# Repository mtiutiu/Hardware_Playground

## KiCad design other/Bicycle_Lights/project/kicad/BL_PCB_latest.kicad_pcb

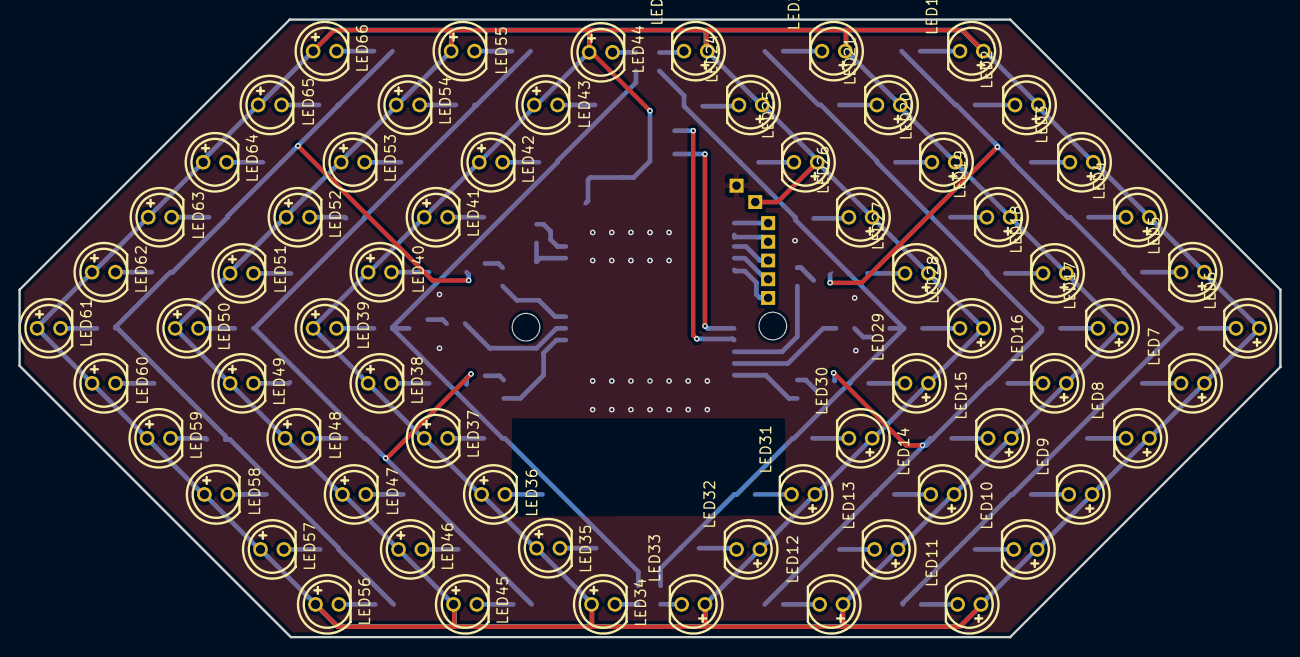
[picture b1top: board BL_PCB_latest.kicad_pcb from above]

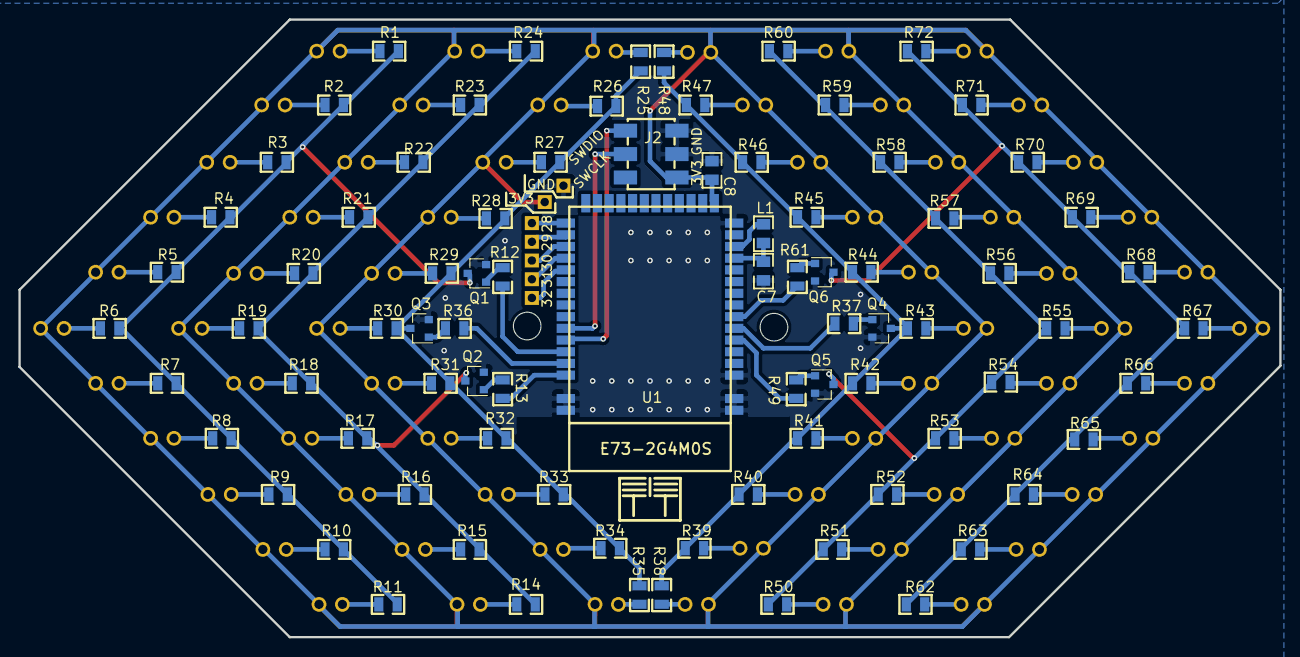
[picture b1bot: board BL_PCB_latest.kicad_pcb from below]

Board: 2 copper layers, 136.9 x 67.1 mm, 150 parts (6 on the bottom side), 90 nets.

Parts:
C7: 1u; 0805
C8: 10u; 0805
J2: SWD; H2X3-SMD-2.54
L1: 10uH; 0805
LED1, LED2, LED3, LED4, LED5, LED6, LED7, LED8, LED9, LED10, LED11, LED12, LED13, LED14, LED15, LED16, LED17, LED18, LED19, LED20, LED21, LED22, LED23, LED24, LED25, LED26, LED27, LED28, LED29, LED30, LED31, LED32, LED33, LED34, LED35, LED36, LED37, LED38, LED39, LED40, LED41, LED42, LED43, LED44, LED45, LED46, LED47, LED48, LED49, LED50, LED51, LED52, LED53, LED54, LED55, LED56, LED57, LED58, LED59, LED60, LED61, LED62, LED63, LED64, LED65, LED66: HL-503S45FC; LED-TH_BD5.0-P2.54-FD
LG: my_logo; ggeac4e8891367b2b2c
Q1, Q2, Q3, Q4, Q5, Q6: MMBT2222; SOT-23
R1, R2, R3, R4, R5, R6, R7, R8, R9, R10, R11, R14, R15, R16, R17, R18, R19, R20, R21, R22, R23, R24, R25, R26, R27, R28, R29, R30, R31, R32, R33, R34, R35, R38, R39, R40, R41, R42, R43, R44, R45, R46, R47, R48, R50, R51, R52, R53, R54, R55, R56, R57, R58, R59, R60, R62, R63, R64, R65, R66, R67, R68, R69, R70, R71, R72: 33; R0805
R12, R13, R36, R37, R49, R61: 1K; R0805
U1: E73-2G4M0S; E73-2G4M04S

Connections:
+3V3: C8.2, J2.1, LED1.1, LED2.1, LED3.1, LED4.1, LED5.1, LED6.1, LED7.1, LED8.1, LED9.1, LED10.1, LED11.1, LED12.1, LED13.1, LED14.1, LED15.1, LED16.1, LED17.1, LED18.1, LED19.1, LED20.1, LED21.1, LED22.1, LED23.1, LED24.1, LED25.1, LED26.1, LED27.1, LED28.1, LED29.1, LED30.1, LED31.1, LED32.1, LED33.1, LED34.1, LED35.1, LED36.1, LED37.1, LED38.1, LED39.1, LED40.1, LED41.1, LED42.1, LED43.1, LED44.1, LED45.1, LED46.1, LED47.1, LED48.1, LED49.1, LED50.1, LED51.1, LED52.1, LED53.1, LED54.1, LED55.1, LED56.1, LED57.1, LED58.1, LED59.1, LED60.1, LED61.1, LED62.1, LED63.1, LED64.1, LED65.1, LED66.1, U1.16
AL1: R12.1, U1.39
AL2: R13.1, U1.41
AL3: R36.1, U1.40
AR1: R37.1, U1.6
AR2: R49.1, U1.5
AR3: R61.1, U1.7
C7_2: C7.2, L1.1, U1.12
GND: C7.1, C8.1, J2.2, J2.3, Q1.2, Q2.2, Q3.2, Q4.2, Q5.2, Q6.2, U1.0, U1.1, U1.2, U1.15, U1.42, U1.43
L1_2: L1.2, U1.13
LED1_2: LED1.2, R1.2
LED2_2: LED2.2, R2.2
LED3_2: LED3.2, R3.2
LED4_2: LED4.2, R4.2
LED5_2: LED5.2, R5.2
LED6_2: LED6.2, R6.2
LED7_2: LED7.2, R7.2
LED8_2: LED8.2, R8.2
LED9_2: LED9.2, R9.2
LED10_2: LED10.2, R10.2
LED11_2: LED11.2, R11.2
LED23_2: LED23.2, R25.2
LED24_2: LED24.2, R26.2
LED25_2: LED25.2, R27.2
LED26_2: LED26.2, R28.2
LED27_2: LED27.2, R29.2
LED28_2: LED28.2, R30.2
LED29_2: LED29.2, R31.2
LED30_2: LED30.2, R32.2
LED31_2: LED31.2, R33.2
LED32_2: LED32.2, R34.2
LED33_2: LED33.2, R35.2
Q1_1: Q1.1, R12.2
Q2_3: Q2.3, R14.1, R15.1, R16.1, R17.1, R18.1, R19.1, R20.1, R21.1, R22.1, R23.1, R24.1
Q3_1: Q3.1, R36.2
Q4_3: Q4.3, R38.1, R39.1, R40.1, R41.1, R42.1, R43.1, R44.1, R45.1, R46.1, R47.1, R48.1
Q5_3: Q5.3, R50.1, R51.1, R52.1, R53.1, R54.1, R55.1, R56.1, R57.1, R58.1, R59.1, R60.1
Q6_3: Q6.3, R62.1, R63.1, R64.1, R65.1, R66.1, R67.1, R68.1, R69.1, R70.1, R71.1, R72.1
R1_1: Q1.3, R1.1, R2.1, R3.1, R4.1, R5.1, R6.1, R7.1, R8.1, R9.1, R10.1, R11.1
R13_2: Q2.1, R13.2
R14_2: LED12.2, R14.2
R15_2: LED13.2, R15.2
R16_2: LED14.2, R16.2
R17_2: LED15.2, R17.2
R18_2: LED16.2, R18.2
R19_2: LED17.2, R19.2
R20_2: LED18.2, R20.2
R21_2: LED19.2, R21.2
R22_2: LED20.2, R22.2
R23_2: LED21.2, R23.2
R24_2: LED22.2, R24.2
R25_1: Q3.3, R25.1, R26.1, R27.1, R28.1, R29.1, R30.1, R31.1, R32.1, R33.1, R34.1, R35.1
R37_2: Q4.1, R37.2
R38_2: LED34.2, R38.2
R39_2: LED35.2, R39.2
R40_2: LED36.2, R40.2
R41_2: LED37.2, R41.2
R42_2: LED38.2, R42.2
R43_2: LED39.2, R43.2
R44_2: LED40.2, R44.2
R45_2: LED41.2, R45.2
R46_2: LED42.2, R46.2
R47_2: LED43.2, R47.2
R48_2: LED44.2, R48.2
R49_2: Q5.1, R49.2
R50_2: LED45.2, R50.2
R51_2: LED46.2, R51.2
R52_2: LED47.2, R52.2
R53_2: LED48.2, R53.2
R54_2: LED49.2, R54.2
R55_2: LED50.2, R55.2
R56_2: LED51.2, R56.2
R57_2: LED52.2, R57.2
R58_2: LED53.2, R58.2
R59_2: LED54.2, R59.2
R60_2: LED55.2, R60.2
R61_2: Q6.1, R61.2
R62_2: LED56.2, R62.2
R63_2: LED57.2, R63.2
R64_2: LED58.2, R64.2
R65_2: LED59.2, R65.2
R66_2: LED60.2, R66.2
R67_2: LED61.2, R67.2
R68_2: LED62.2, R68.2
R69_2: LED63.2, R69.2
R70_2: LED64.2, R70.2
R71_2: LED65.2, R71.2
R72_2: LED66.2, R72.2
SWCLK: J2.5, U1.37
SWDIO: J2.4, U1.38

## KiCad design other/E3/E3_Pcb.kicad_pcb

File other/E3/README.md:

### Ender-3 Controller Board Remake

#### 3D renderings of pcb

Top view | Bottom view
------------ | -------------
 | 

Designed using **EasyEDA** and ported to **KiCAD** (**PCB** only) using the awesome [easyeda2kicad](<https://github.com/wokwi/easyeda2kicad>) tool.

#### Hardware revisions:

- 0.1 - initial design
- 0.2 - fixed/optimized power traces width
- 0.3 - changelog:
  - expose thermal pads
  - BOOT0 connect via pull-down resistor
  - simplified usb interface
  - added power support via USB for MCU

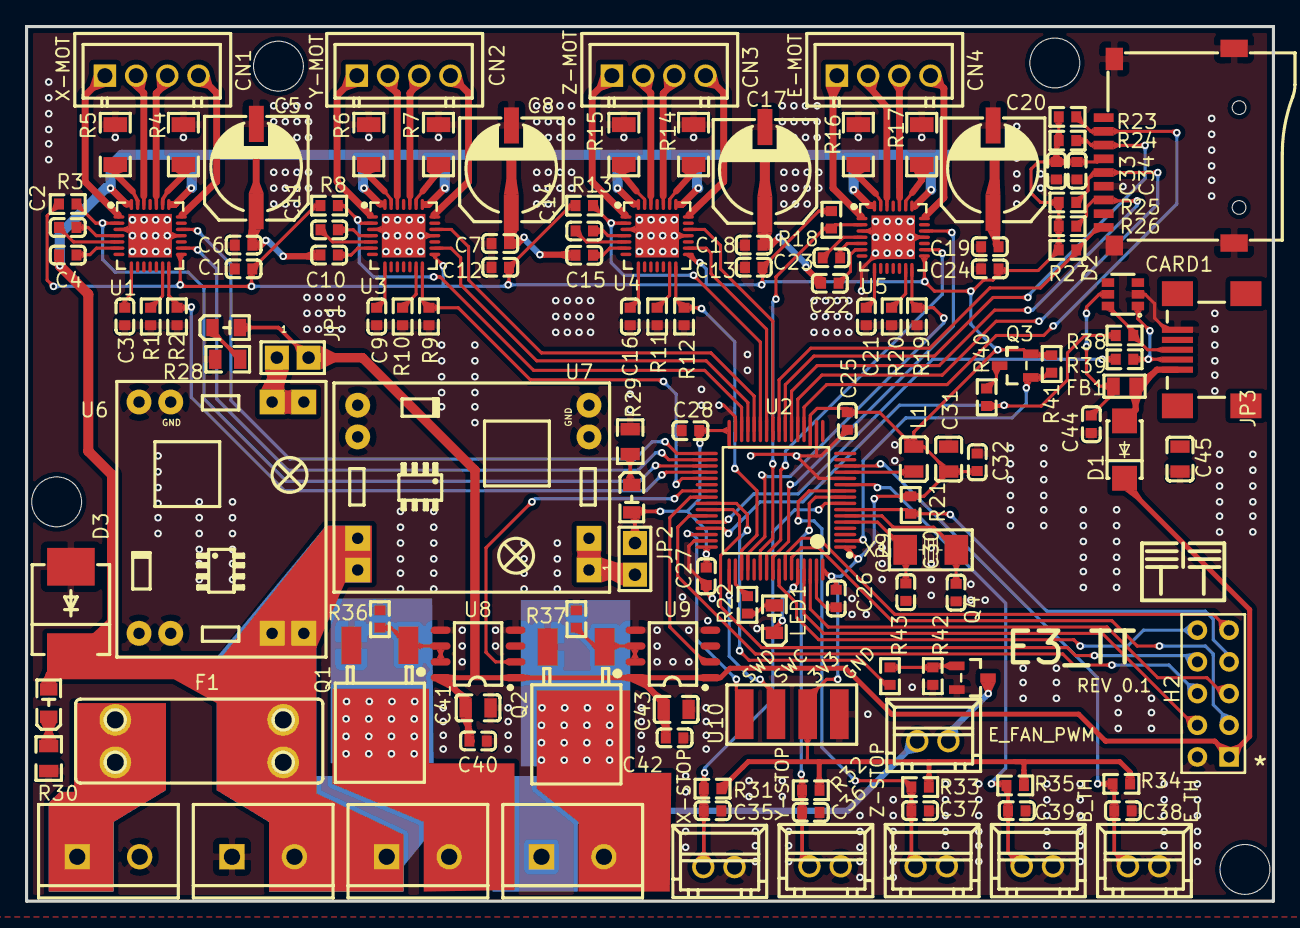
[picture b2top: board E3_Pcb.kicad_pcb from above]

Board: 2 copper layers, 99.9 x 70.1 mm, 133 parts (0 on the bottom side), 112 nets.

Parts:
ALG: my_logo; ggeac4e8891367b2b2c
C1, C4, C6, C7, C10, C12, C13, C15, C18, C19, C22, C24, C25, C26, C27, C28, C32, C34, C35, C36, C37, C40, C42, C44: 100nF; C0603
C2, C11, C14, C23: 22nF; C0603
C3, C9, C16, C21, C33: 4.7uF; C0603
C5, C8, C17, C20: 100uF; CAP-SMD_BD8.0-L8.3-W8.3-FD
C29, C30: 36pF; C0603
C31, C41, C43: 10uF; C0805
C38, C39: 10uF; C0603
C45: 4.7nF; C0805
CARD1: microSD; TF-SMD_TF-15×15
CN1, CN2, CN3, CN4: XH-4AK M; CONN-TH_4P-P2.50_XH-4A
CN5: X-STOP; CONN-TH_XH-2A
CN6: Y-STOP; CONN-TH_XH-2A
CN7: Z-STOP; CONN-TH_XH-2A
CN8: B_TH; CONN-TH_XH-2A
CN9: E_TH; CONN-TH_XH-2A
CN10: E_FAN_PWM; CONN-TH_XH-2A
D1: SS34; DO-214AC_L4.3-W2.7-LS5.3-RD
D2: NUP2114; TSOP-6_L3.0-W1.5-P0.95-LS2.8-BL
D3: SS36; SMC_L7.1-W6.2-LS8.1-RD
F1: 20A; KEYSTONE 3557-2
FB1: MH2029-300Y; L0805
H2: LCD; HDR-TH_10P-P2.54-V-R2-C5-S2.54
JP1, JP2: 1; JUMPER2
JP3: USB_MINI; USB-MINIB
L1: 22uH; L0805
LED1: STATUS; LED0805-RD
LED2: 5V_PWR; LED0805-RD
LED3: 3V3_PWR; LED0805-RD
LED4: PWR_IN; LED0805-RD
P1: PWR-IN; SCREWTERMINAL-5MM-2
P2: E_PWM; SCREWTERMINAL-5MM-2
P3: B_PWM; SCREWTERMINAL-5MM-2
P4: PWR-OUT; SCREWTERMINAL-5MM-2
Q1, Q2: IRLR8726TRPBF; TO-252-2_L6.6-W6.1-P4.57-LS9.9-BR-CW
Q3: IRLML2244TRPBF; SOT-23-3_L2.9-W1.6-P1.90-LS2.8-BR
Q4: IRLML6346TRPBF; SOT-23-3_L2.9-W1.6-P1.90-LS2.8-BR
R1, R2, R3, R8, R9, R10, R11, R12, R13, R18, R19, R20: 20K; R0603
R4, R5, R6, R7, R14, R15, R16, R17: 0.18; R1206
R21, R22, R34, R35: 4.7K; R0603
R23, R24, R25, R26, R31, R32, R33: 10K; R0603
R27: 1.8K; R0603
R28: 680; R0805
R29: 330; R0805
R30: 4.7K; R0805
R36, R37, R42: 100K; R0603
R38, R39: 27; R0603
R40, R41: 1.5K; R0603
R43: 10Ω; R0603
U1, U3, U4, U5: TMC2208-LA-T; QFN-28_L5.0-W5.0-P0.50-BL-EP
U2: STM32F103RCT6; LQFP-64_L10.0-W10.0-P0.50-LS12.0-BL
U6, U7: GND; MP1584 STEP DOWN MODULE - PCB
U8, U9: MCP1407-E/SN; SOP-8_L4.9-W3.9-P1.27-LS6.0-BL
U10: ICSP; SMD PIN HEADER 1X4
X1: 8MHz; OSC-SMD_L5.0-W3.2

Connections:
+3V3: C1.2, C12.2, C13.2, C24.2, C25.1, C26.1, C27.1, C28.1, C31.1, C32.2, C33.1, C34.1, CARD1.4, JP2.2, L1.1, LED3.2, Q3.2, R3.2, R8.2, R13.2, R18.2, R21.2, R23.2, R24.2, R25.2, R26.2, R27.2, R31.1, R32.1, R33.1, R34.2, R35.2, R41.2, U1.15, U2.1, U2.19, U2.32, U2.48, U2.64, U3.15, U4.15, U5.15, U10.2
+5V: C40.1, C41.1, C42.1, C43.1, D1.1, H2.1, JP1.2, LED2.2, U8.1, U8.8, U9.1, U9.8
+VB: C4.2, C5.1, C6.2, C7.2, C8.1, C10.2, C15.2, C17.1, C18.2, C19.2, C20.1, C22.2, CN10.1, D3.2, F1.2, LED4.2, P2.1, P3.1, P4.2, U1.22, U1.28, U3.22, U3.28, U4.22, U4.28, U5.22, U5.28, U6.2, U7.2
BED_PWM: U2.40, U9.2
C9_1: C9.1, U3.8
C10_1: C10.1, U3.6
C11_1: C11.1, U3.4
C11_2: C11.2, U3.5
C21_1: C21.1, U5.8
C22_1: C22.1, U5.6
C23_1: C23.1, U5.4
C23_2: C23.2, U5.5
C44_1: C44.1, D2.5, FB1.2
D2_1: D2.1, JP3.D-, R39.1
D2_6: D2.6, JP3.D+, R38.1
E0_DIR: U2.56, U5.19
E0_EN: R18.1, U2.54, U5.2
E0_OA1: CN4.3, U5.24
E0_OA2: CN4.4, U5.21
E0_OB1: CN4.2, U5.26
E0_OB2: CN4.1, U5.1
E0_STP: U2.55, U5.16
E0_UART: R19.2, U2.52, U5.14
F1_1: F1.1, P1.1
FAN_PWM: R43.1, U2.41
FB1_1: D1.2, FB1.1, JP3.VBUS
GND: C1.1, C3.2, C5.2, C6.1, C7.1, C8.2, C9.2, C12.1, C13.1, C16.2, C17.2, C18.1, C19.1, C20.2, C21.2, C24.1, C25.2, C26.2, C27.2, C28.2, C29.1, C30.1, C31.2, C32.1, C33.2, C34.2, C35.2, C36.2, C37.2, C38.2, C39.2, C40.2, C41.2, C42.2, C43.2, C44.2, C45.2, CARD1.6, CARD1.10, CARD1.11, CARD1.12, CARD1.13, CN5.2, CN6.2, CN7.2, CN8.2, CN9.2, D2.2, D3.1, H2.2, JP3.GND, LED1.1, P1.2, P4.1, Q1.3, Q2.3, Q4.2, R1.2, R2.1, R4.2, R5.2, R6.2, R7.2, R9.1, R10.2, R11.2, R12.1, R14.2, R15.2, R16.2, R17.2, R19.1, R20.2, R28.1, R29.1, R30.2, R36.1, R37.1, R42.1, U1.3, U1.18, U1.29, U2.12, U2.18, U2.31, U2.47, U2.60, U2.63, U3.3, U3.18, U3.29, U4.3, U4.18, U4.29, U5.3, U5.18, U5.29, U6.1, U6.4, U7.1, U7.4, U8.4, U8.5, U9.4, U9.5, U10.1
HE0_PWM: U2.39, U8.2
LCD_BEEP: H2.10, U2.57
LCD_CS: H2.4, U2.61
LCD_ENC_A: H2.6, U2.43
LCD_ENC_B: H2.8, U2.42
LCD_ENC_BTN: H2.9, U2.58
LCD_MOSI: H2.3, U2.59
LCD_SCK: H2.5, U2.62
Q1_2: P2.2, Q1.2
Q2_2: P3.2, Q2.2
Q3_3: Q3.3, R40.1
Q4_1: Q4.1, R42.2, R43.2
Q4_3: CN10.2, Q4.3
R10_1: R10.1, U3.13
R20_1: R20.1, U5.13
R22_2: LED1.2, R22.2
R28_2: LED2.1, R28.2
R29_2: LED3.1, R29.2
R30_1: LED4.1, R30.1
R37_2: Q2.1, R37.2, U9.6, U9.7
RESET: H2.7, R21.1, U2.7
SD_CS: CARD1.2, R23.1, U2.20
SD_DET: CARD1.9, R27.1, U2.24
SD_MISO: CARD1.7, R26.1, U2.22
SD_MOSI: CARD1.3, R24.1, U2.23
SD_SCK: CARD1.5, R25.1, U2.21
STATUS: R22.1, U2.50
SWCLK: U2.49, U10.3
SWDIO: U2.46, U10.4
TH0: C38.1, CN9.1, R34.1, U2.14
THB: C39.1, CN8.1, R35.1, U2.11
U1_4: C2.1, U1.4
U1_5: C2.2, U1.5
U1_6: C4.1, U1.6
U1_8: C3.1, U1.8
U1_13: R1.1, U1.13
U1_23: R4.1, U1.23
U1_27: R5.1, U1.27
U2_5: C29.2, U2.5, X1.1
U2_6: C30.2, U2.6, X1.2
U2_13: L1.2, U2.13
U3_23: R7.1, U3.23
U3_27: R6.1, U3.27
U4_4: C14.1, U4.4
U4_5: C14.2, U4.5
U4_6: C15.1, U4.6
U4_8: C16.1, U4.8
U4_13: R11.1, U4.13
U4_23: R14.1, U4.23
U4_27: R15.1, U4.27
U5_23: R17.1, U5.23
U5_27: R16.1, U5.27
U6_3: JP1.1, U6.3
U7_3: JP2.1, U7.3
U8_6: Q1.1, R36.2, U8.6, U8.7
USB_CONN: Q3.1, R41.1, U2.2
USB_D+: R38.2, R40.2, U2.45
USB_D-: R39.2, U2.44
X_DIR: U1.19, U2.33
X_EN: R3.1, U1.2, U2.35
X_OA1: CN1.3, U1.24
X_OA2: CN1.4, U1.21
X_OB1: CN1.2, U1.26
X_OB2: CN1.1, U1.1
X_STOP: C35.1, CN5.1, R31.2, U2.8
X_STP: U1.16, U2.34
X_UART: R2.2, U1.14, U2.36
Y_DIR: U2.28, U3.19
Y_EN: R8.1, U2.30, U3.2
Y_OA1: CN2.3, U3.24
Y_OA2: CN2.4, U3.21
Y_OB1: CN2.2, U3.26
Y_OB2: CN2.1, U3.1
Y_STOP: C36.1, CN6.1, R32.2, U2.9
Y_STP: U2.29, U3.16
Y_UART: R9.2, U2.37, U3.14
Z_DIR: U2.25, U4.19
Z_EN: R13.1, U2.27, U4.2
Z_OA1: CN3.3, U4.24
Z_OA2: CN3.4, U4.21
Z_OB1: CN3.2, U4.26
Z_OB2: CN3.1, U4.1
Z_STOP: C37.1, CN7.1, R33.2, U2.10
Z_STP: U2.26, U4.16
Z_UART: R12.2, U2.51, U4.14

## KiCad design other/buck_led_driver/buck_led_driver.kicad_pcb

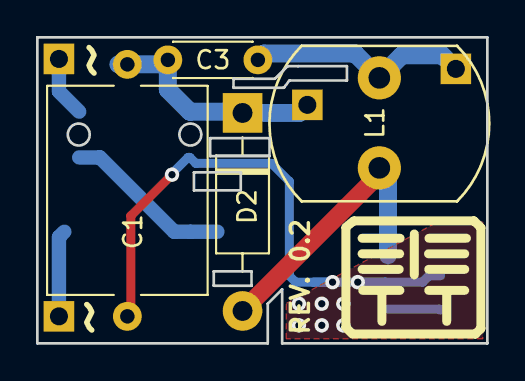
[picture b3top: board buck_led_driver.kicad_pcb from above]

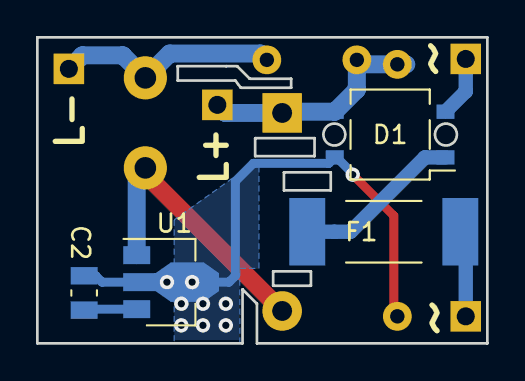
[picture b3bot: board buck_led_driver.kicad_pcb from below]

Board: 2 copper layers, 25.0 x 17.0 mm, 12 parts (4 on the bottom side), 8 nets.

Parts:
C1: 100n/400Vdc; C_Rect_L11.5mm_W8.8mm_P10.00mm_MKT
C2: 0.1u; C_0805_2012Metric
C3: 10n/100Vdc; C_Disc_D4.3mm_W1.9mm_P5.00mm
D1: MB10S; TO-269AA
D2: MUR160; D_DO-41_SOD81_P10.16mm_Horizontal
F1: 0.5A; R_2512_6332Metric
J1, J2: AC_IN; PinHeader_1x01_P2.54mm_Vertical
J3: LED+; PinHeader_1x01_P2.54mm_Vertical
J4: LED-; PinHeader_1x01_P2.54mm_Vertical
L1: 39mH; L_Radial_D12.0mm_P5.00mm_Neosid_SD12k_style2
U1: HV9922N8-G; SOT-89-3

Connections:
GND: C1.2, C2.1, D1.4, U1.2
unnamed: C1.1, C3.1, D1.3, D2.1, J3.1
unnamed: C2.2, U1.3
unnamed: C3.2, J4.1, L1.1
unnamed: D1.1, F1.1
unnamed: D1.2, J1.1
unnamed: D2.2, L1.2, U1.1
unnamed: F1.2, J2.1

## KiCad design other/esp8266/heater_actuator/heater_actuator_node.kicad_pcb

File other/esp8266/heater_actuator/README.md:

## ESP8266 heater actuator module

##### 3D renderings of pcb

Top view | Bottom view
------------ | -------------
 | 

**Description:**

This is a ESP8266 actuator node for controlling a heater or other appliances using a relay.

 **Kindly notice:**

The only thing I ask if using this project is to at least mention my name and if I don't ask too much you can also support my effort using the below button. Thanks for buying me a beer :).

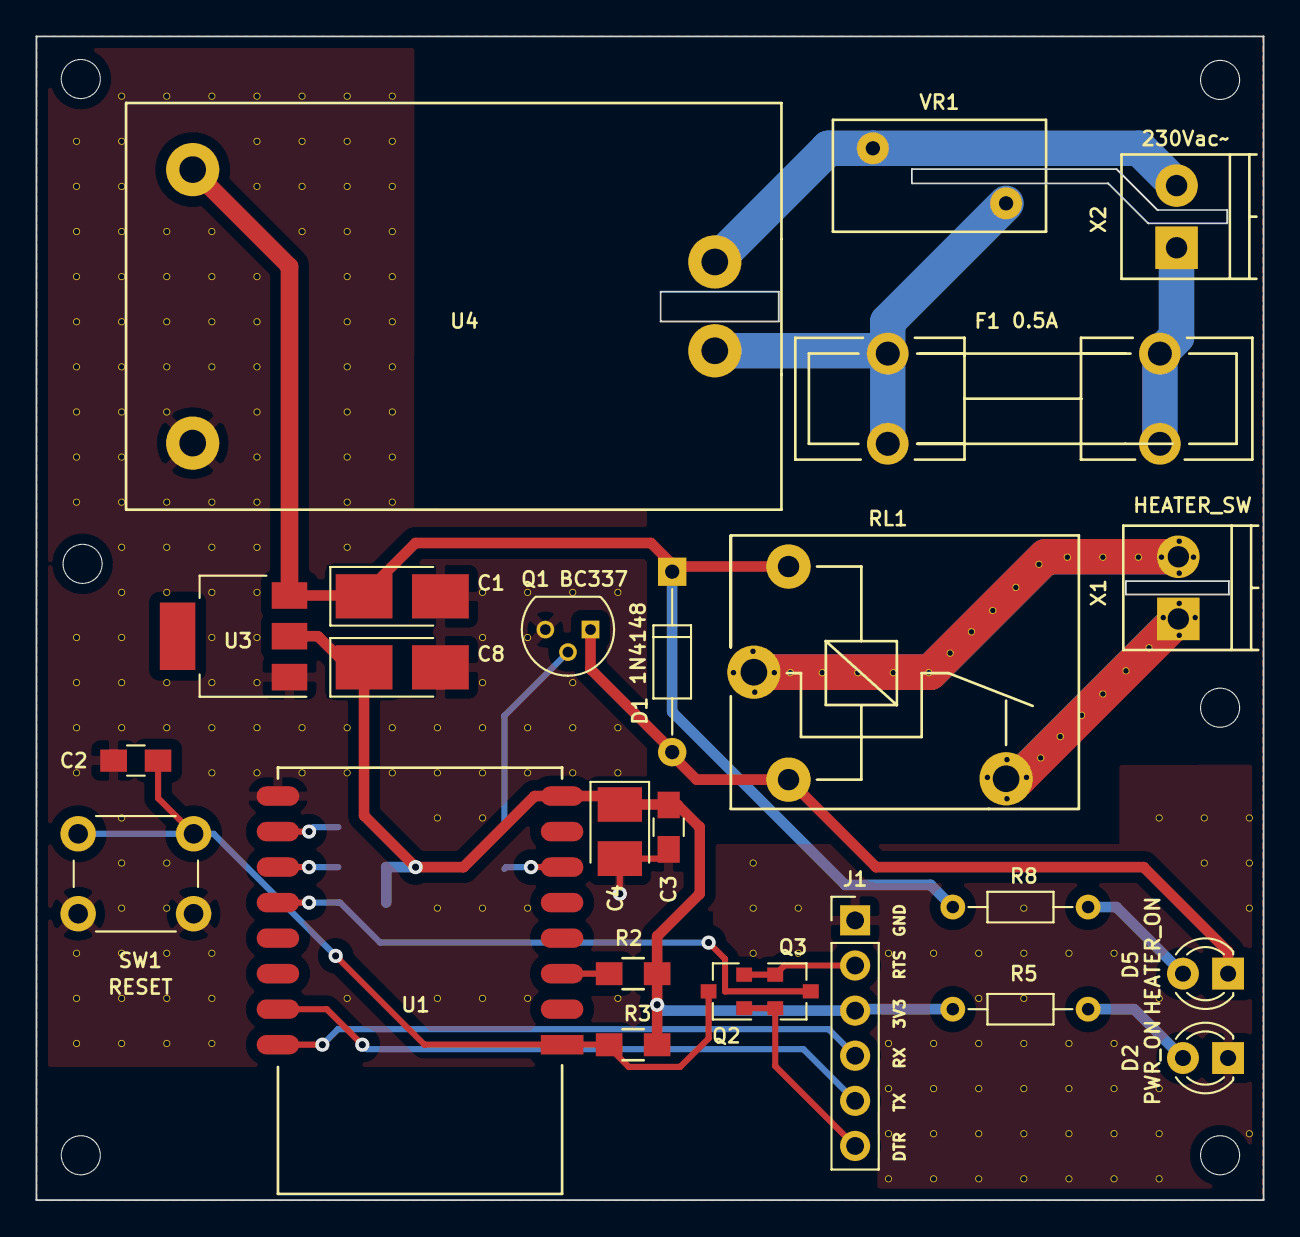
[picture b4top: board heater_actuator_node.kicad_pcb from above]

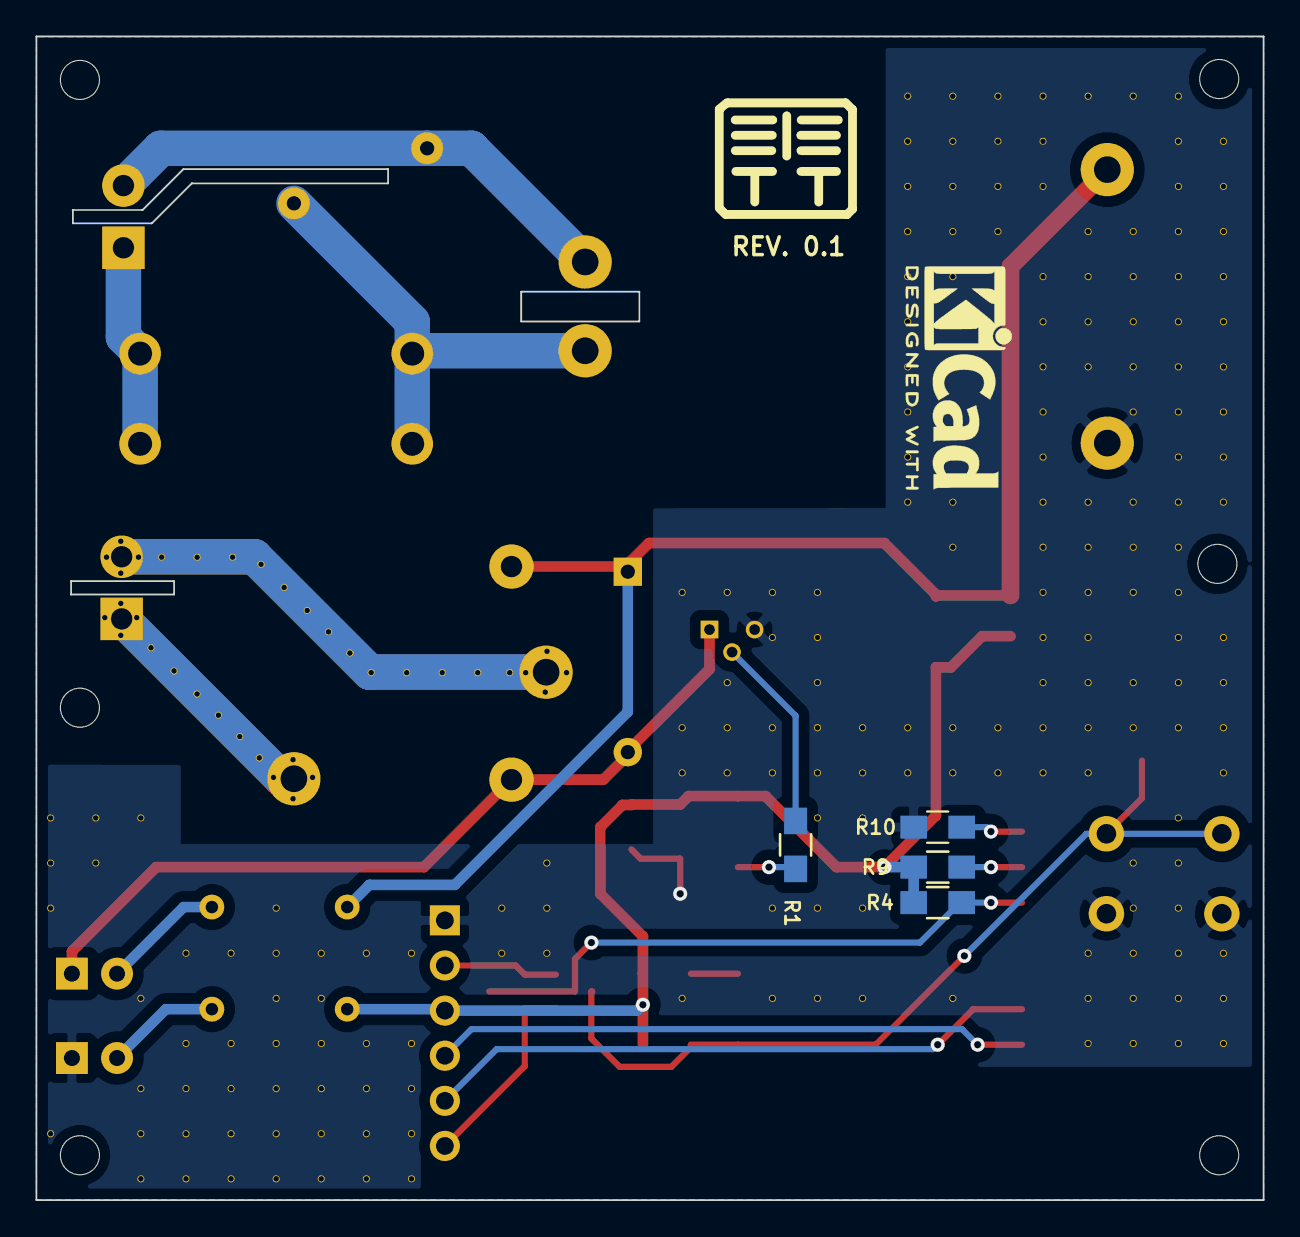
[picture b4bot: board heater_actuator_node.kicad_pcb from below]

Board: 2 copper layers, 69.1 x 65.5 mm, 255 parts (4 on the bottom side), 22 nets.

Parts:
C1, C8: 22u; CP_Tantalum_Case-B_EIA-3528-21_Hand
C2, C3: 100n; C_0805_HandSoldering
C4: 22u; CP_Tantalum_Case-B_EIA-3528-21_Reflow
D1: 1N4148; D_DO-35_SOD27_P10.16mm_Horizontal
D2: PWR_ON; LED_D3.0mm
D5: HEATER_ON; LED_D3.0mm
F1: 0.5A; Fuseholder5x20_horiz_open_lateral_Type-II
J1: Conn_01x06; Pin_Header_Straight_1x06_Pitch2.54mm
Q1: BC337; TO-92_Molded_Narrow
Q2, Q3: MMBT3904; SOT-23
R1: 5K6; R_0805_HandSoldering
R2, R3, R4, R9, R10: 10K; R_0805_HandSoldering
R5, R8: 330; R_Axial_DIN0204_L3.6mm_D1.6mm_P7.62mm_Horizontal
RL1: RM50-SP; RM50_SP
SW1: RESET; SW_PUSH_6mm
U1: ESP-12
U3: AMS1117-3.3; SOT-223
U4: HLK-PM01
V3_3, V3_4, V3_5, V3_6, V3_7, V3_8, V3_9, V3_10, V3_11, V3_14, V3_15, V3_16, V3_17, V3_21, V3_22, V3_23, V4_2, V4_3, V4_4, V4_5, V4_6, V4_7, V4_8, V4_9, V4_10, V4_11, V4_12, V4_13, V4_14, V4_15, V4_16, V4_18, V4_19, V4_20, V4_21, V4_22, V4_23, V5_2, V5_5, V5_6, V5_7, V5_8, V5_9, V5_11, V5_12, V5_13, V5_15, V5_16, V5_19, V5_20, V5_21, V5_22, V5_23, V6_2, V6_5, V6_6, V6_7, V6_8, V6_11, V6_12, V6_13, V6_14, V6_15, V6_16, V6_17, V6_21, V6_22, V6_23, V7_2, V7_3, V7_4, V7_6, V7_7, V7_8, V7_9, V7_10, V7_11, V7_12, V7_13, V7_14, V7_15, V7_16, V7_17, V8_2, V8_3, V8_4, V8_5, V8_16, V8_17, V9_2, V9_3, V9_4, V9_5, V9_6, V9_7, V9_8, V9_9, V9_10, V9_11, V9_12, V9_16, V9_17, V9_22, V10_2, V10_3, V10_4, V10_5, V10_6, V10_7, V10_8, V10_9, V10_10, V10_11, V10_16, V10_17, V11_16, V11_17, V11_18, V11_20, V11_22, V12_13, V12_14, V12_15, V12_16, V12_17, V12_18, V12_20, V12_22, V13_13, V13_14, V13_16, V13_17, V13_20, V13_22, V14_13, V14_15, V14_16, V14_17, V15_13, V15_16, V15_17, V15_22, V18_19, V18_20, V18_21, V19_20, V19_21, V21_21, V21_23, V21_24, V21_25, V21_26, V22_21, V22_23, V22_24, V22_25, V22_26, V23_21, V23_22, V23_23, V23_24, V23_25, V23_26, V24_20, V24_21, V24_22, V24_23, V24_24, V24_25, V24_26, V25_21, V25_23, V25_24, V25_25, V25_26, V26_21, V26_23, V26_24, V26_25, V26_26, V27_18, V27_18#2, V27_18#3, V27_18#4, V27_18#5, V27_18#6, V27_18#7, V27_18#8, V27_18#9, V27_18#10, V27_18#11, V27_18#12, V27_18#13, V27_18#14, V27_18#15, V27_18#16, V27_18#17, V27_18#18, V27_18#19, V27_18#20, V27_18#21, V27_18#22, V27_18#23, V27_18#24, V27_18#25, V27_18#26, V27_18#27, V27_18#28, V27_18#29, V27_18#30, V27_18#31, V27_18#32, V27_18#33, V27_18#34, V27_18#35, V27_18#36, V27_22, V27_24, V27_25, V27_26, V28_18, V28_19, V29_18, V29_19, V29_20, V29_25: AUTO_VIA; VIA_MATRIX
VR1: VAR10-300; RV_Disc_D12_W6.3_P7.5
X1: HEATER_SW; TerminalBlock_Pheonix_PT-3.5mm_2pol
X2: 230Vac~~; TerminalBlock_Pheonix_PT-3.5mm_2pol

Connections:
+3V3: C3.1, C4.1, C8.1, J1.3, R2.2, R3.2, R4.2, R5.1, R9.2, U1.8, U3.2
+5V: C1.1, D1.1, R8.1, RL1.A1, U3.3, U4.3
/DTR: J1.6, Q2.1, Q3.2
/EN: R2.1, U1.3
/GPIO0: Q3.3, R4.1, U1.12
/GPIO2: R9.1, U1.11
/GPIO15: R10.1, U1.10
/H_RELAY_CMD: R1.2, U1.6
/RESET: C2.1, Q2.3, R3.1, SW1.1, U1.1
/RTS: J1.2, Q2.2, Q3.1
/RX: J1.4, U1.16
/TX: J1.5, U1.15
GND: C1.2, C2.2, C3.2, C4.2, C8.2, D2.1, J1.1, Q1.3, R10.2, SW1.2, U1.9, U3.1, U4.4, V3_3.1, V3_4.1, V3_5.1, V3_6.1, V3_7.1, V3_8.1, V3_9.1, V3_10.1, V3_11.1, V3_14.1, V3_15.1, V3_16.1, V3_17.1, V3_21.1, V3_22.1, V3_23.1, V4_2.1, V4_3.1, V4_4.1, V4_5.1, V4_6.1, V4_7.1, V4_8.1, V4_9.1, V4_10.1, V4_11.1, V4_12.1, V4_13.1, V4_14.1, V4_15.1, V4_16.1, V4_18.1, V4_19.1, V4_20.1, V4_21.1, V4_22.1, V4_23.1, V5_2.1, V5_5.1, V5_6.1, V5_7.1, V5_8.1, V5_9.1, V5_11.1, V5_12.1, V5_13.1, V5_15.1, V5_16.1, V5_19.1, V5_20.1, V5_21.1, V5_22.1, V5_23.1, V6_2.1, V6_5.1, V6_6.1, V6_7.1, V6_8.1, V6_11.1, V6_12.1, V6_13.1, V6_14.1, V6_15.1, V6_16.1, V6_17.1, V6_21.1, V6_22.1, V6_23.1, V7_2.1, V7_3.1, V7_4.1, V7_6.1, V7_7.1, V7_8.1, V7_9.1, V7_10.1, V7_11.1, V7_12.1, V7_13.1, V7_14.1, V7_15.1, V7_16.1, V7_17.1, V8_2.1, V8_3.1, V8_4.1, V8_5.1, V8_16.1, V8_17.1, V9_2.1, V9_3.1, V9_4.1, V9_5.1, V9_6.1, V9_7.1, V9_8.1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
unnamed: D1.2, D5.1, Q1.1, RL1.A2
unnamed: D2.2, R5.2
unnamed: D5.2, R8.2
unnamed: F1.1, U4.1, VR1.1
unnamed: F1.2, X2.1
unnamed: Q1.2, R1.1
unnamed: RL1.11, V27_18.1, V27_18#2.1, V27_18#3.1, V27_18#18.1, V27_18#19.1, V27_18#20.1, V27_18#21.1, V27_18#22.1, V27_18#23.1, V27_18#24.1, V27_18#25.1, V27_18#26.1, V27_18#27.1, V27_18#28.1, V27_18#29.1, V27_18#30.1, V27_18#31.1, V27_18#32.1, V27_18#33.1, V27_18#34.1, V27_18#35.1, X1.2
unnamed: RL1.14, V27_18#4.1, V27_18#5.1, V27_18#6.1, V27_18#7.1, V27_18#8.1, V27_18#9.1, V27_18#10.1, V27_18#11.1, V27_18#12.1, V27_18#13.1, V27_18#14.1, V27_18#15.1, V27_18#16.1, V27_18#17.1, X1.1
unnamed: U4.2, VR1.2, X2.2

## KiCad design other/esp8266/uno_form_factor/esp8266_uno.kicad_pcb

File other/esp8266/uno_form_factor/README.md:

## ESP8266 Arduino UNO

##### 3D renderings of pcb

Top view | Bottom view
------------ | -------------
 | 

**Description:**

ESP8266 board in Arduino UNO format(support for ESP-12 series OR WROOM).

 **Kindly notice:**

The only thing I ask if using this project is to at least mention my name and if I don't ask too much you can also support my effort using the below button. Thanks for buying me a beer :).

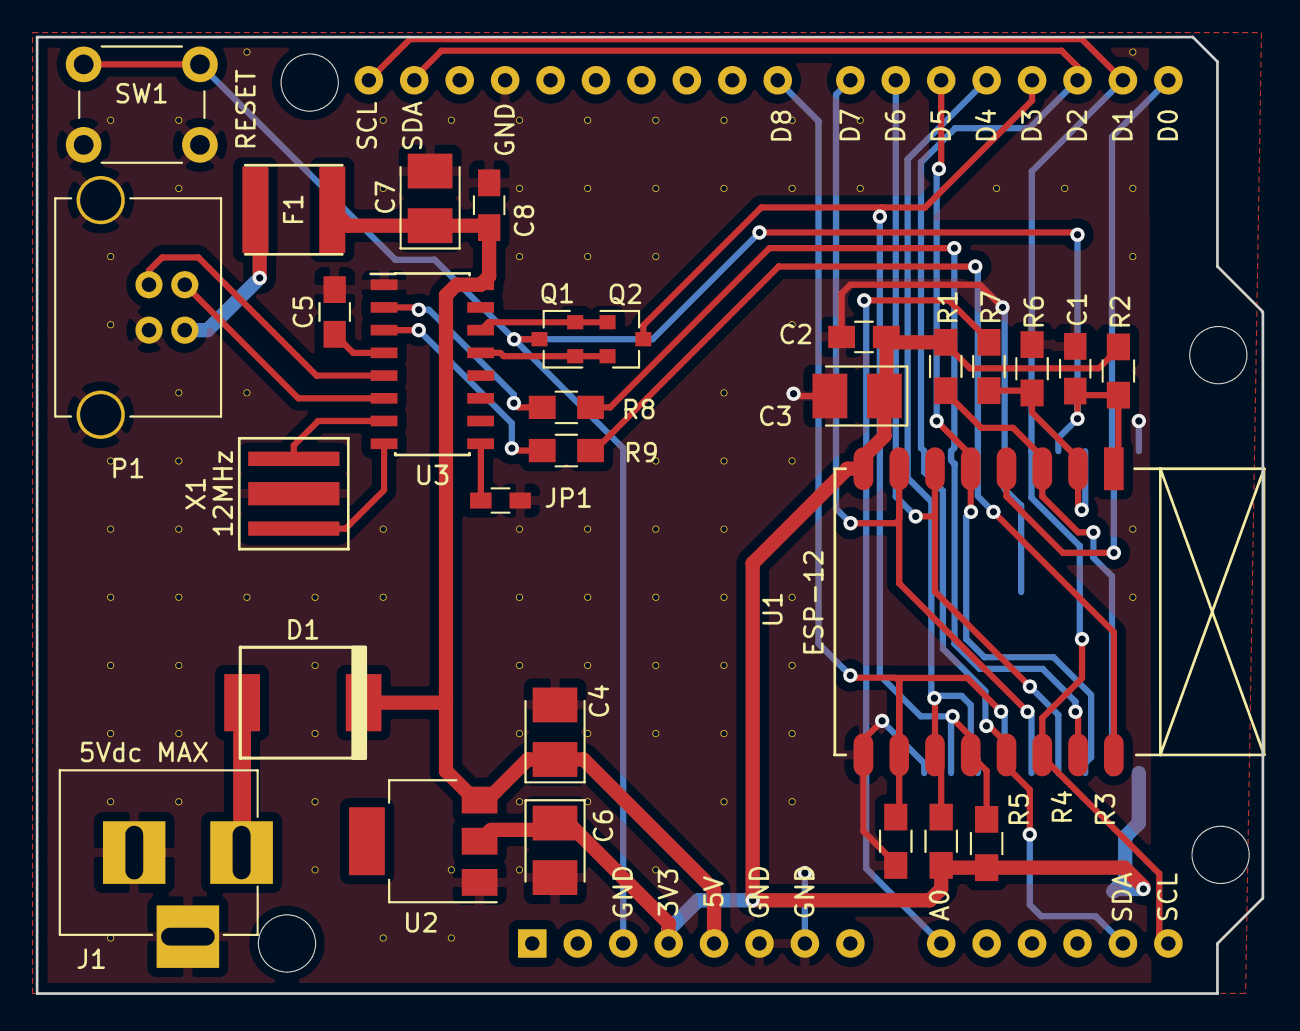
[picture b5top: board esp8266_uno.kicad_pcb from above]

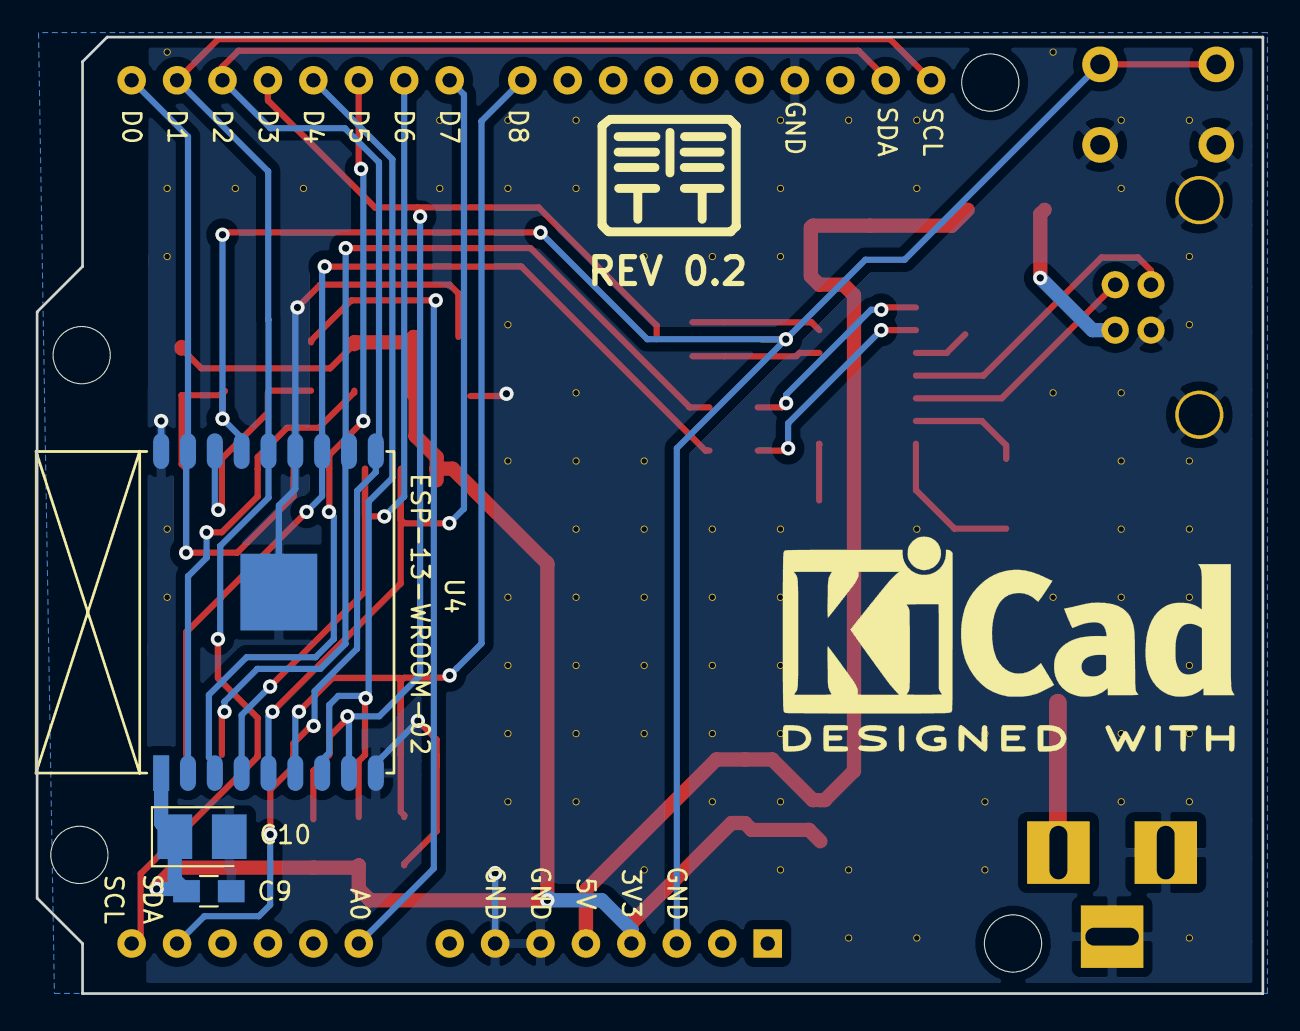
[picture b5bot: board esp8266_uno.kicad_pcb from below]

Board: 2 copper layers, 68.5 x 53.5 mm, 120 parts (4 on the bottom side), 30 nets.

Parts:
A1: Arduino_UNO_R3
C1, C2, C8, C9: 100n; C_0805_HandSoldering
C3, C7, C10: 10u; CP_Tantalum_Case-B_EIA-3528-21_Reflow
C4, C6: 22u; CP_Tantalum_Case-B_EIA-3528-21_Reflow
C5: 10n; C_0805_HandSoldering
D1: SS34; do214ab
F1: MF-SMDF050; mf-smdf050
J1: Barrel_Jack; BARREL_JACK
JP1: CTS; R_0603_HandSoldering
P1: USB; USB_B
Q1, Q2: 2N2222; SOT-23
R1, R2, R3, R4, R5: 10K; R_0805_HandSoldering
R6: 100K; R_0805_HandSoldering
R7: 220K; R_0805_HandSoldering
R8, R9: 470; R_0805_HandSoldering
SW1: RESET; SW_PUSH_6mm
U1: ESP-12
U2: AMS1117-3.3; SOT-223
U3: CH340G; SOIC-16_3.9x9.9mm_Pitch1.27mm
U4: ESP-13-WROOM-02
V3_2, V3_4, V3_5, V3_7, V3_8, V3_9, V3_10, V3_11, V3_12, V3_14, V4_2, V4_3, V4_6, V4_7, V4_8, V4_9, V4_10, V4_11, V4_12, V5_1, V5_6, V5_9, V6_9, V6_10, V6_11, V6_12, V6_13, V7_2, V7_3, V7_8, V7_9, V7_14, V8_2, V8_13, V8_14, V9_2, V9_3, V9_4, V9_8, V9_9, V9_10, V9_11, V9_12, V9_13, V10_2, V10_3, V10_4, V10_8, V10_9, V10_10, V10_11, V10_12, V11_2, V11_3, V11_4, V11_7, V11_8, V11_9, V11_10, V11_11, V11_13, V12_2, V12_3, V12_6, V12_7, V12_8, V12_9, V12_10, V12_11, V12_12, V13_2, V13_3, V13_5, V13_7, V13_9, V13_10, V13_11, V13_12, V14_2, V14_3, V16_3, V17_3, V18_1, V18_3, V18_4, V18_8, V18_9: AUTO_VIA; VIA_MATRIX
X1: 12MHz; ZTTCS-3

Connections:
+3V3: A1.4, C2.2, C3.1, C6.1, C9.2, C10.1, R1.2, R2.2, R3.2, R4.2, U1.8, U2.2, U4.1
+5V: A1.5, C4.1, C7.1, C8.2, D1.1, F1.1, U2.3, U3.16
/A0: A1.9, R7.1
/ADC: R6.1, R7.2, U1.2, U4.16
/DTR: Q1.1, Q2.2, U3.13
/EN: R1.1, U1.3, U4.2
/GPIO0: A1.18, Q2.3, R3.1, U1.12, U4.8
/GPIO2: A1.19, R4.1, U1.11, U4.7
/GPIO4: A1.13, A1.17, A1.31, U1.13, U4.10
/GPIO5: A1.14, A1.16, A1.32, U1.14, U4.14
/GPIO12: A1.21, U1.6, U4.4
/GPIO13: A1.22, U1.7, U4.5
/GPIO14: A1.20, U1.5, U4.3
/GPIO15: A1.23, R5.1, U1.10, U4.6
/GPIO16: A1.15, U1.4, U4.17
/RESET: A1.3, C1.2, Q1.3, R2.1, SW1.1, U1.1, U4.15
/RTS: Q1.2, Q2.1, U3.14
/RX: R8.2, U1.15, U4.11
/TX: R9.2, U1.16, U4.12
GND: A1.6, A1.7, A1.29, C1.1, C2.1, C3.2, C4.2, C5.2, C6.2, C7.2, C8.1, C9.1, C10.2, J1.2, J1.3, JP1.1, P1.4, P1.5, R5.2, R6.2, SW1.2, U1.9, U2.1, U3.1, U4.9, U4.13, U4.18, U4.PAD, V3_2.1, V3_4.1, V3_5.1, V3_7.1, V3_8.1, V3_9.1, V3_10.1, V3_11.1, V3_12.1, V3_14.1, V4_2.1, V4_3.1, V4_6.1, V4_7.1, V4_8.1, V4_9.1, V4_10.1, V4_11.1, V4_12.1, V5_1.1, V5_6.1, V5_9.1, V6_9.1, V6_10.1, V6_11.1, V6_12.1, V6_13.1, V7_2.1, V7_3.1, V7_8.1, V7_9.1, V7_14.1, V8_2.1, V8_13.1, V8_14.1, V9_2.1, V9_3.1, V9_4.1, V9_8.1, V9_9.1, V9_10.1, V9_11.1, V9_12.1, V9_13.1, V10_2.1, V10_3.1, V10_4.1, V10_8.1, V10_9.1, V10_10.1, V10_11.1, V10_12.1, V11_2.1, V11_3.1, V11_4.1, V11_7.1, V11_8.1, V11_9.1, V11_10.1, V11_11.1, V11_13.1, V12_2.1, V12_3.1, V12_6.1, V12_7.1, V12_8.1, V12_9.1, V12_10.1, V12_11.1, V12_12.1, V13_2.1, V13_3.1, V13_5.1, V13_7.1, V13_9.1, V13_10.1, V13_11.1, V13_12.1, V14_2.1, V14_3.1, V16_3.1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
unnamed: C5.1, U3.4
unnamed: D1.2, J1.1
unnamed: F1.2, P1.1
unnamed: JP1.2, U3.9
unnamed: P1.2, U3.6
unnamed: P1.3, U3.5
unnamed: R8.1, U3.2
unnamed: R9.1, U3.3
unnamed: U3.7, X1.1
unnamed: U3.8, X1.3

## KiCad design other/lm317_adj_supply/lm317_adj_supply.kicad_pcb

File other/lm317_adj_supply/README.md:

## LM317 Adjustable Power Supply (30V/5A)

##### 3D renderings of pcb

Top view |
------------ |

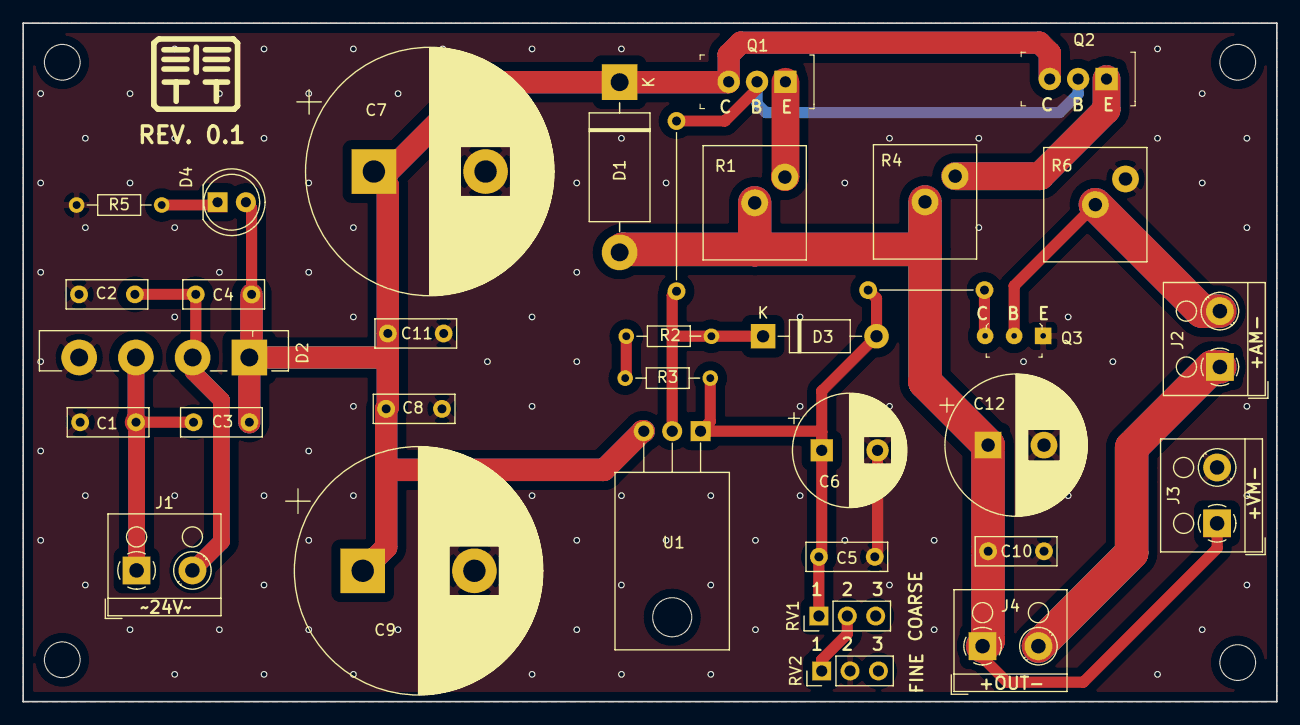
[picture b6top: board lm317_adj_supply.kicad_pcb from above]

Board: 2 copper layers, 112.2 x 60.8 mm, 32 parts (0 on the bottom side), 14 nets.

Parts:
C1, C2, C3, C4, C5, C8, C10, C11: 0.1u/63V; C_Rect_L7.2mm_W2.5mm_P5.00mm_FKS2_FKP2_MKS2_MKP2
C6: 150u/50V; CP_Radial_D10.0mm_P5.00mm
C7, C9: 3300u/50V; CP_Radial_D22.0mm_P10.00mm_SnapIn
C12: 1000u/50V; CP_Radial_D12.5mm_P5.00mm
D1: MUR420; D_DO-201AD_P15.24mm_Horizontal
D2: GBU8M; Diode_Bridge_Vishay_GBU
D3: 1N4007; D_DO-41_SOD81_P10.16mm_Horizontal
D4: PWR_LED; LED_D5.0mm
J1: TR(24Vac); TerminalBlock_RND_205-00001_1x02_P5.00mm_Horizontal
J2: AMP_MEAS; TerminalBlock_RND_205-00001_1x02_P5.00mm_Horizontal
J3: VOLT_MEAS; TerminalBlock_RND_205-00001_1x02_P5.00mm_Horizontal
J4: V_REG_OUT; TerminalBlock_RND_205-00001_1x02_P5.00mm_Horizontal
Q1, Q2: TIP41C; TO-220-3
Q3: BC337; TO-92-3_Formed_Leads
R1, R4, R6: 0.12/5W; R_Radial_Power_L9.0mm_W10.0mm_Px2.70mm_Py2.30mm
R2, R3: 120; R_Axial_DIN0204_L3.6mm_D1.6mm_P7.62mm_Horizontal
R5: 6K8; R_Axial_DIN0204_L3.6mm_D1.6mm_P7.62mm_Horizontal
RV1: 5K; PinHeader_1x03_P2.54mm_Vertical
RV2: 500; PinHeader_1x03_P2.54mm_Vertical
U1: LM317; TO-220-3_Horizontal

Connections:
/V_REG_IN: C3.2, C4.1, C7.1, C8.1, C9.1, C11.1, D1.1, D2.1, D4.2, Q1.3, Q2.3, U1.3
GND: C1.2, C2.1, C5.2, C6.2, C7.2, C8.2, C9.2, C10.2, C11.2, C12.2, D2.4, J3.2, Q3.1, R5.2, R6.2, RV2.2
unnamed: C1.1, C3.1, D2.3, J1.1
unnamed: C2.2, C4.2, D2.2, J1.2
unnamed: C5.1, C6.1, D3.2, Q3.3, R3.2, RV1.1, U1.1
unnamed: C10.1, C12.1, D1.2, J3.1, J4.1, R1.1, R4.1
unnamed: D3.1, Q1.2, Q2.2, R2.1, U1.2
unnamed: D4.1, R5.1
unnamed: J2.1, J4.2
unnamed: J2.2, Q3.2, R6.1
unnamed: Q1.1, R1.2
unnamed: Q2.1, R4.2
unnamed: R2.2, R3.1
unnamed: RV1.2, RV2.1
